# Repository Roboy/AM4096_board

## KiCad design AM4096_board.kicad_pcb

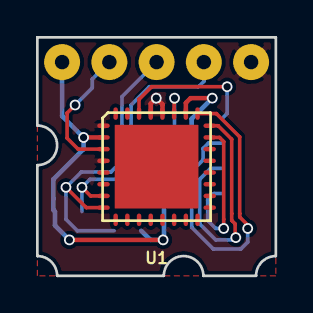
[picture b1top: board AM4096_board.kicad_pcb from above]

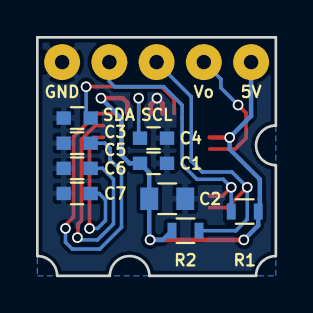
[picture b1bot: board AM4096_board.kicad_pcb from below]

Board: 2 copper layers, 13.2 x 13.2 mm, 15 parts (14 on the bottom side), 10 nets.

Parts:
5V: Vdd; SolderWirePad_single_0-8mmDrill
C1, C3, C4, C5: 100n; C_0603
C2: 2.2u; C_0805
C6, C7: 10n; C_0603
GND: Gnd; SolderWirePad_single_0-8mmDrill
R1, R2: 47k; R_0603
SCL: SCL; SolderWirePad_single_0-8mmDrill
SDA: SDA; SolderWirePad_single_0-8mmDrill
U1: ATMEGA328PB-MU; QFN32_6x6mm_Pitch0.65mm
Vo: V_Out; SolderWirePad_single_0-8mmDrill

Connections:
GND: C1.1, C2.2, C3.1, C4.2, C5.2, C6.1, C7.1, GND.1, U1.1, U1.4, U1.17, U1.28, U1.29
unnamed: C3.2, U1.30
unnamed: C4.1, U1.27
unnamed: C5.1, U1.25
unnamed: C6.2, U1.24
unnamed: C7.2, U1.23
unnamed: R1.2, SDA.1, U1.7
unnamed: R2.2, SCL.1, U1.8
unnamed: U1.3, Vo.1
VCC: 5V.1, C1.2, C2.1, R1.1, R2.1, U1.2, U1.26

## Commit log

2017-06-08 Initial commit with more or less finished schematic
2017-06-08 Started PCB layout
2017-06-25 Finished routing and corrected layout so that the center of the magnet sits on the center of the board. No screws possible ...
2017-06-27 Added mounting holes (M2)
2017-07-06 Reexported 3D models
2019-01-22 Added some images.
